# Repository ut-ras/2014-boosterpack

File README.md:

2014-boosterpack
================
This repo contains the eagle source for a boosterpack designed for the Stellaris/Tiva lm4f/tm4c launchpads.

TODO
================
* buck regulator circuit for bat -> vbus of launchpad
* buck regulator circuit for bat -> 5V servos
* headers for the launchpad
* motor driver circuit for driving two motors from battery power
* headers of power, ground, signal trios

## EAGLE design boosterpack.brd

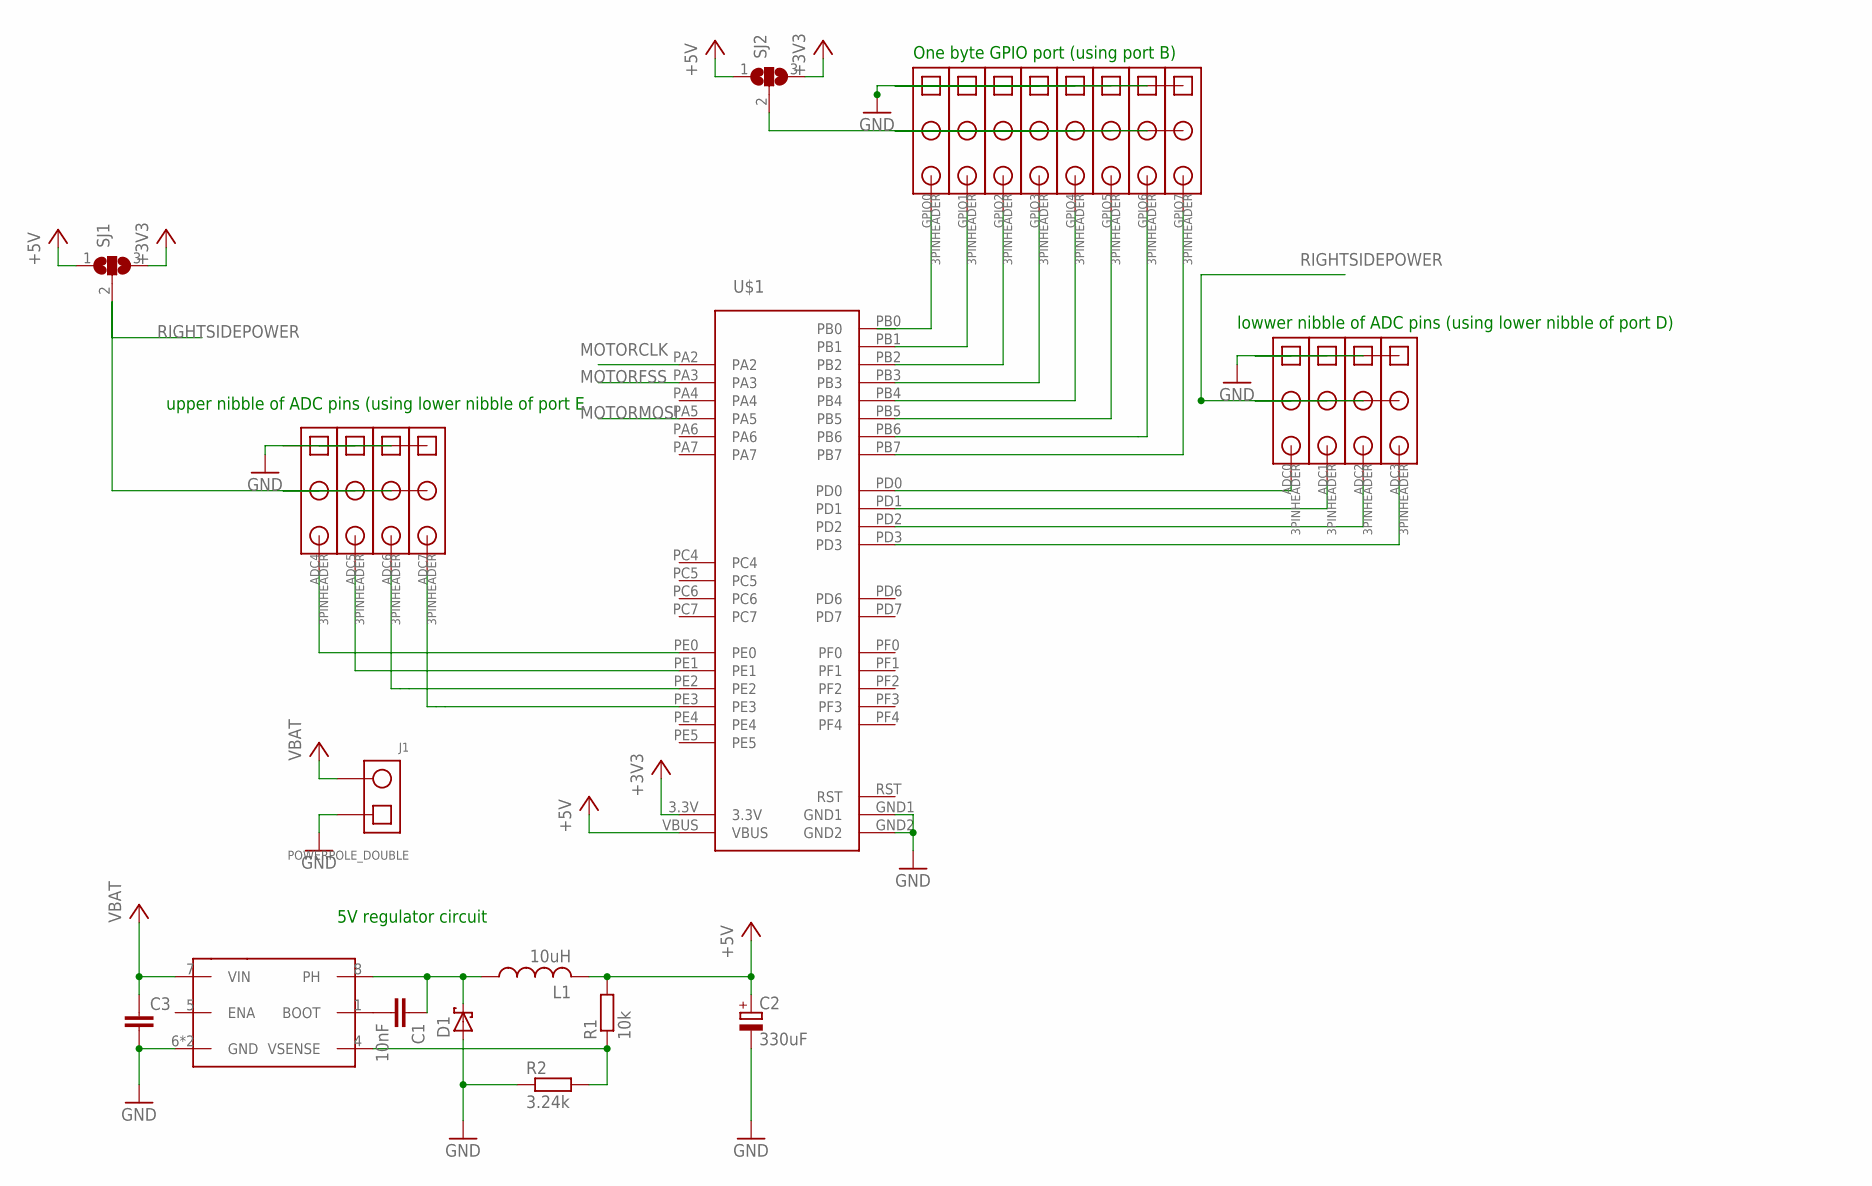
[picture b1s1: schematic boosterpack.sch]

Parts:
ADC0, ADC1, ADC2, ADC3, ADC4, ADC5, ADC6, ADC7: 3PINHEADER
C1: 10nF; C025-024X044
C2: 330uF; B45181A
C3: C-EU025-024X044; C025-024X044
D1: SCHOTTKY-DIODEDO35-7; DO35-7
GPIO0, GPIO1, GPIO2, GPIO3, GPIO4, GPIO5, GPIO6, GPIO7: 3PINHEADER
J1: POWERPOLE_DOUBLE
L1: 10uH; SDR1006
R1: 10k; 0204/5
R2: 3.24k; 0204/5
SJ1, SJ2: SJ2W; SJ_2
U$1: STELLARIS-LAUNCHPADSTELLARIS-LAUNCHPAD-XL; LAUNCHPAD-XL
U$2: TPS5450; DDS

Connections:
+3V3: SJ1.3, SJ2.3, U$1.3.3V
+5V: C2.+, L1.P$2 (2), R1.2, SJ1.1, SJ2.1, U$1.VBUS
ADC1: ADC1.3, U$1.PD1
ADC2: ADC2.3, U$1.PD2
ADC3: ADC3.3, U$1.PD3
ADC5: ADC5.3, U$1.PE1
GND: ADC0.1, ADC1.1, ADC2.1, ADC3.1, ADC4.1, ADC5.1, ADC6.1, ADC7.1, C2.-, C3.2, D1.A, GPIO0.1, GPIO1.1, GPIO2.1, GPIO3.1, GPIO4.1, GPIO5.1, GPIO6.1, GPIO7.1, J1.1, R2.1, U$1.GND1, U$1.GND2, U$2.6 (GND), U$2.GROUNDPAD (GND)
GPIO0: GPIO0.3, U$1.PB0
GPIO1: GPIO1.3, U$1.PB1
GPIO2: GPIO2.3, U$1.PB2
GPIO3: GPIO3.3, U$1.PB3
MOTORCLK: U$1.PA2
MOTORFSS: U$1.PA3
MOTORMOSI: U$1.PA5
unnamed: ADC0.3, U$1.PD0
unnamed: GPIO4.3, U$1.PB4
unnamed: GPIO5.3, U$1.PB5
unnamed: ADC6.3, U$1.PE2
unnamed: ADC7.3, U$1.PE3
unnamed: GPIO6.3, U$1.PB6
unnamed: GPIO0.2, GPIO1.2, GPIO2.2, GPIO3.2, GPIO4.2, GPIO5.2, GPIO6.2, GPIO7.2, SJ2.2
unnamed: GPIO7.3, U$1.PB7
unnamed: C1.2, U$2.1 (BOOT)
unnamed: R1.1, R2.2, U$2.4 (VSENSE)
unnamed: C1.1, D1.C, L1.P$1 (1), U$2.8 (PH)
unnamed: ADC4.3, U$1.PE0
RIGHTSIDEPOWER: ADC0.2, ADC1.2, ADC2.2, ADC3.2, ADC4.2, ADC5.2, ADC6.2, ADC7.2, SJ1.2
RST: U$1.RST
VCC: C3.1, J1.2, U$2.7 (VIN)

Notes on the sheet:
One byte GPIO port (using port B)
lowwer nibble of ADC pins (using lower nibble of port D)
upper nibble of ADC pins (using lower nibble of port E
5V regulator circuit

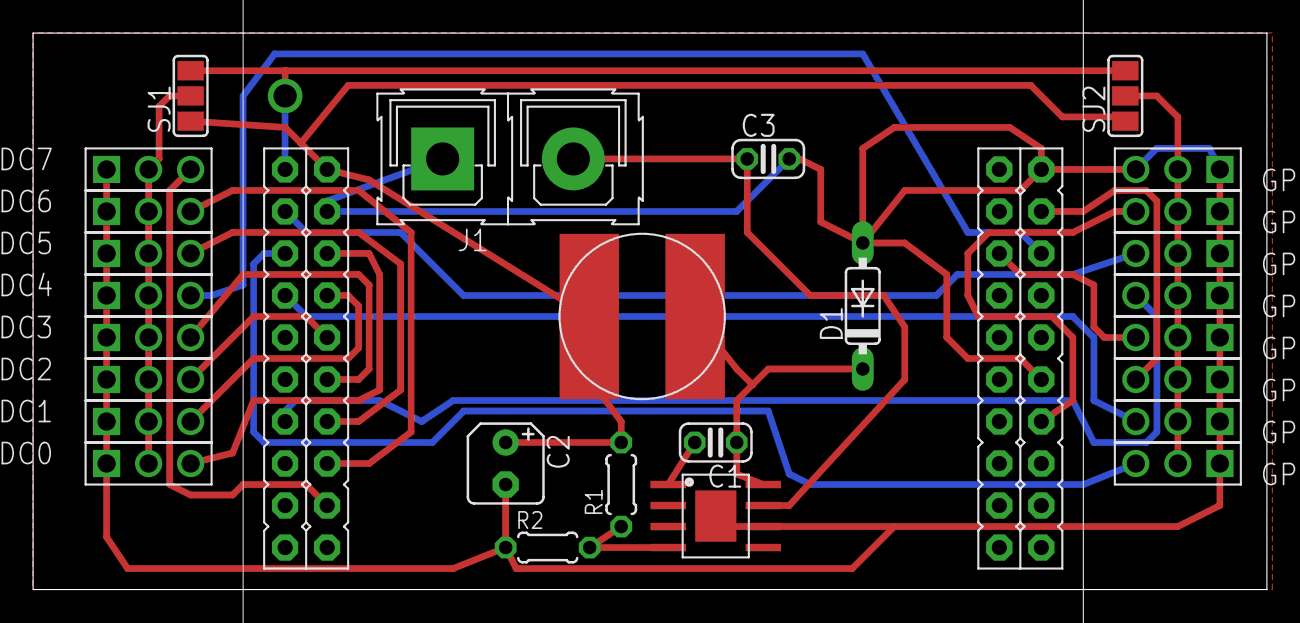
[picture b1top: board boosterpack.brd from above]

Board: 2 copper layers, 74.6 x 33.6 mm, 28 parts (0 on the bottom side), 25 nets.

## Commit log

2014-04-25 inital eagle project created
2014-04-25 created a readme with my todo list
2014-04-25 added inital schematic which specifies the pin assignments for the two bytes of direct IO
2014-04-25 inital layout of the header on the 'board'
2014-04-25 added power regulating circiut
2014-04-25 new layout for the reg circuit
    I feel like explaining my use of the smd inductor
    * it's small ~10mm wide by ~6mm tall
    * it's easy to solder (it's a huge smd part afterall)
    * it's cheip $0.60
    * it makes putting the regulator under the launchpad possible
    * it brings down the surface area by about half compared to other parts
2014-04-25 lots of routing; moustly just routing
2014-04-26 flipped the adc's and the gpio's; fewer wires are going across the middle
2014-04-26 added diode i forgot; routed new diode
2014-04-28 added spi motor driver for two motors
2014-04-29 fixed 3v3 not connecting to the motor drivers and rerouted some stuff
2014-04-29 added mounting holes; moved motors to a better spot
2014-11-24 Removed motor drivers, almost done wiring board
